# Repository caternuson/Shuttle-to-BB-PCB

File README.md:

# Shuttle-to-BB-PCB
Breadboard adapter for Bosch Sensortec Shuttle Boards.

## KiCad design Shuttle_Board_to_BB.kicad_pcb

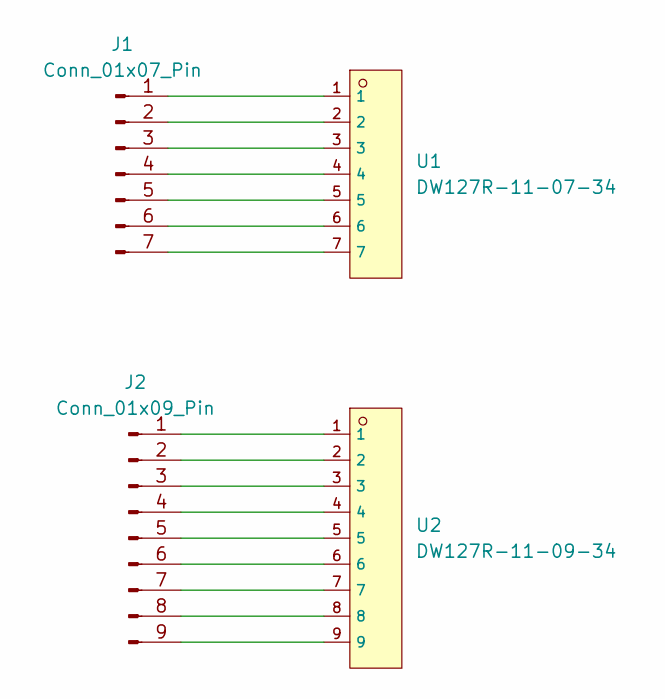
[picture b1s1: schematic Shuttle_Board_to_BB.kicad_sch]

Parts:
J1: Conn_01x07_Pin; PinHeader_1x07_P2.54mm_Vertical
J2: Conn_01x09_Pin; PinHeader_1x09_P2.54mm_Vertical
U1: DW127R-11-07-34; HDR-TH_7P-P1.27-V-F; LCSC C2935877
U2: DW127R-11-09-34; HDR-TH_9P-P1.27-V-F; LCSC C2935879

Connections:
unnamed: J1.1, U1.1
unnamed: J1.2, U1.2
unnamed: J1.3, U1.3
unnamed: J1.4, U1.4
unnamed: J1.5, U1.5
unnamed: J1.6, U1.6
unnamed: J1.7, U1.7
unnamed: J2.1, U2.1
unnamed: J2.2, U2.2
unnamed: J2.3, U2.3
unnamed: J2.4, U2.4
unnamed: J2.5, U2.5
unnamed: J2.6, U2.6
unnamed: J2.7, U2.7
unnamed: J2.8, U2.8
unnamed: J2.9, U2.9

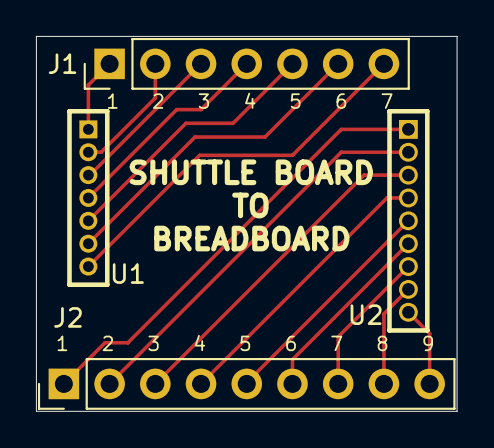
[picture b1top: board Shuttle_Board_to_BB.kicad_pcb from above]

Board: 2 copper layers, 23.4 x 20.8 mm, 4 parts (0 on the bottom side), 16 nets.
